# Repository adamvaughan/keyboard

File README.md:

Low profile, alice-like keyboard.

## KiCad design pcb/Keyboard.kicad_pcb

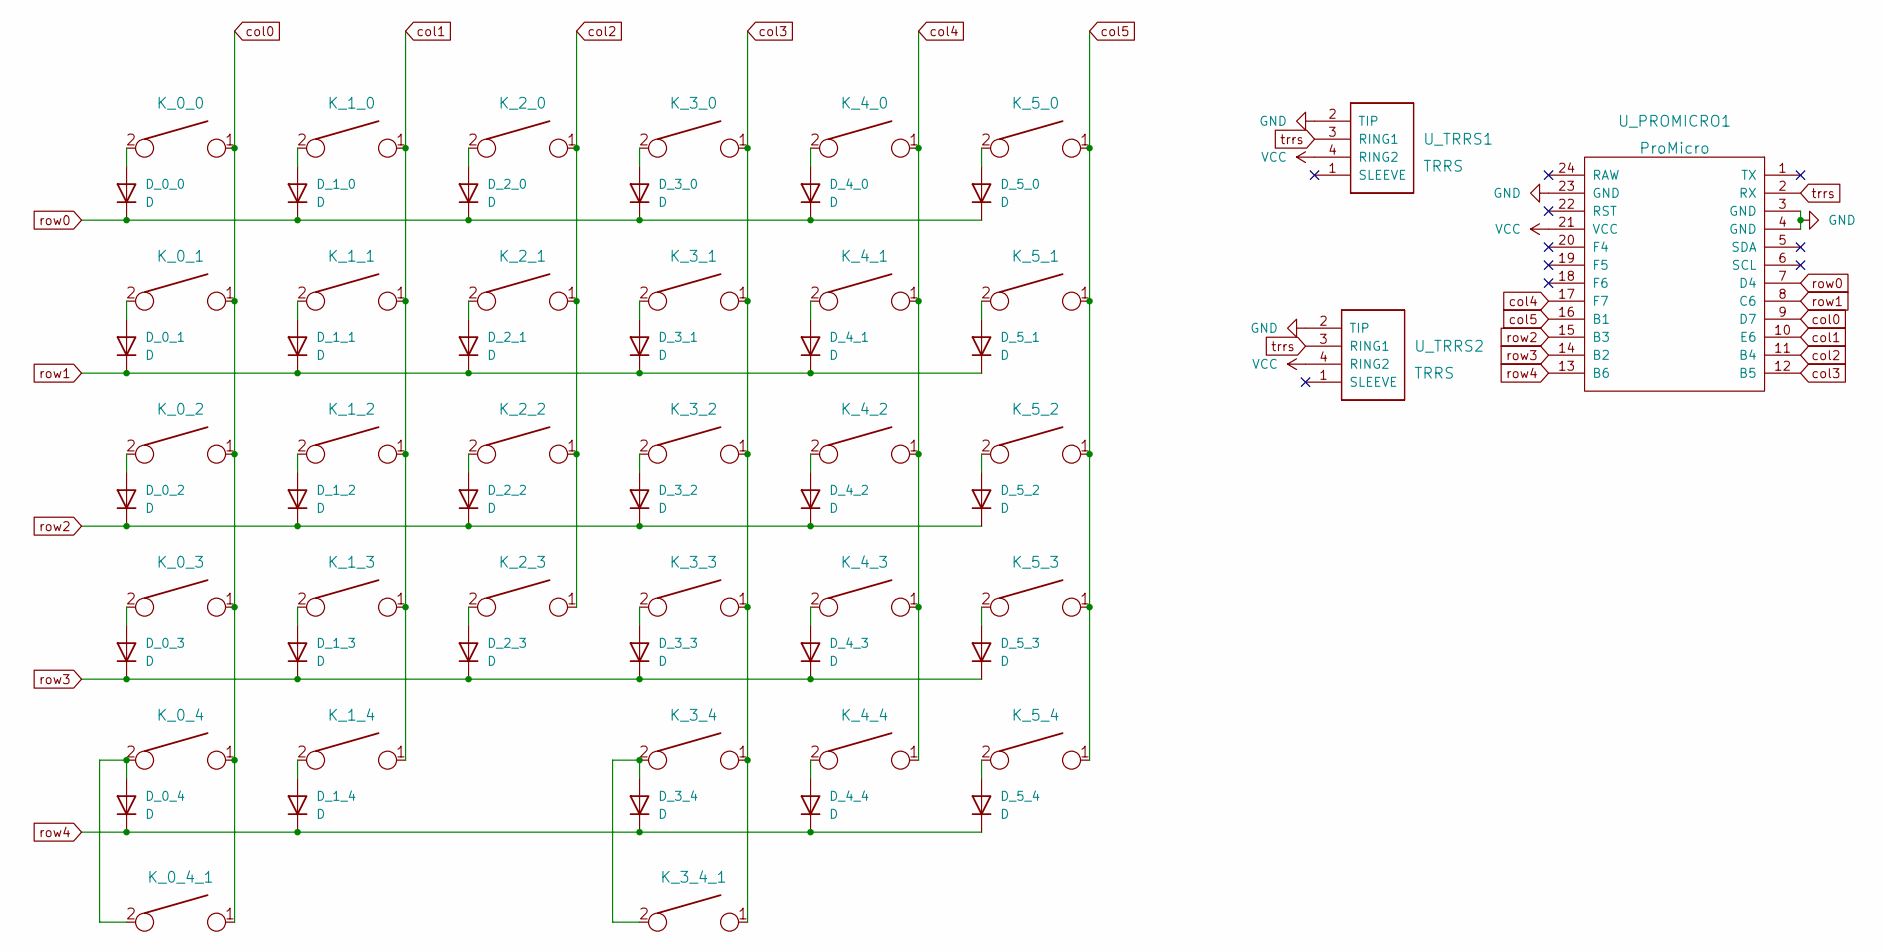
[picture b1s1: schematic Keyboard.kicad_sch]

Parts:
D_0_0, D_0_1, D_0_2, D_0_3, D_0_4, D_1_0, D_1_1, D_1_2, D_1_3, D_1_4, D_2_0, D_2_1, D_2_2, D_2_3, D_3_0, D_3_1, D_3_2, D_3_3, D_3_4, D_4_0, D_4_1, D_4_2, D_4_3, D_4_4, D_5_0, D_5_1, D_5_2, D_5_3, D_5_4: D; D_SOD123
K_0_0, K_0_1, K_0_2, K_0_3, K_0_4, K_0_4_1, K_1_0, K_1_1, K_1_2, K_1_3, K_1_4, K_2_0, K_2_1, K_2_2, K_2_3, K_3_0, K_3_1, K_3_2, K_3_3, K_3_4, K_3_4_1, K_4_0, K_4_1, K_4_2, K_4_3, K_4_4, K_5_0, K_5_1, K_5_2, K_5_3, K_5_4: KEYSW; SW_Hotswap_Kailh_Choc_V1_1.00u
U_PROMICRO1: ProMicro
U_TRRS1, U_TRRS2: TRRS; TRRS-PJ-320A

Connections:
GND: U_PROMICRO1.3 (GND), U_PROMICRO1.4 (GND), U_PROMICRO1.23 (GND), U_TRRS1.2 (TIP), U_TRRS2.2 (TIP)
unnamed: D_0_0.2 (A), K_0_0.2
unnamed: D_0_1.2 (A), K_0_1.2
unnamed: D_0_2.2 (A), K_0_2.2
unnamed: D_0_3.2 (A), K_0_3.2
unnamed: D_0_4.2 (A), K_0_4.2, K_0_4_1.2
unnamed: D_1_0.2 (A), K_1_0.2
unnamed: D_1_1.2 (A), K_1_1.2
unnamed: D_1_2.2 (A), K_1_2.2
unnamed: D_1_3.2 (A), K_1_3.2
unnamed: D_1_4.2 (A), K_1_4.2
unnamed: D_2_0.2 (A), K_2_0.2
unnamed: D_2_1.2 (A), K_2_1.2
unnamed: D_2_2.2 (A), K_2_2.2
unnamed: D_2_3.2 (A), K_2_3.2
unnamed: D_3_0.2 (A), K_3_0.2
unnamed: D_3_1.2 (A), K_3_1.2
unnamed: D_3_2.2 (A), K_3_2.2
unnamed: D_3_3.2 (A), K_3_3.2
unnamed: D_3_4.2 (A), K_3_4.2, K_3_4_1.2
unnamed: D_4_0.2 (A), K_4_0.2
unnamed: D_4_1.2 (A), K_4_1.2
unnamed: D_4_2.2 (A), K_4_2.2
unnamed: D_4_3.2 (A), K_4_3.2
unnamed: D_4_4.2 (A), K_4_4.2
unnamed: D_5_0.2 (A), K_5_0.2
unnamed: D_5_1.2 (A), K_5_1.2
unnamed: D_5_2.2 (A), K_5_2.2
unnamed: D_5_3.2 (A), K_5_3.2
unnamed: D_5_4.2 (A), K_5_4.2
VCC: U_PROMICRO1.21 (VCC), U_TRRS1.4 (RING2), U_TRRS2.4 (RING2)
col0: K_0_0.1, K_0_1.1, K_0_2.1, K_0_3.1, K_0_4.1, K_0_4_1.1, U_PROMICRO1.9 (D7)
col1: K_1_0.1, K_1_1.1, K_1_2.1, K_1_3.1, K_1_4.1, U_PROMICRO1.10 (E6)
col2: K_2_0.1, K_2_1.1, K_2_2.1, K_2_3.1, U_PROMICRO1.11 (B4)
col3: K_3_0.1, K_3_1.1, K_3_2.1, K_3_3.1, K_3_4.1, K_3_4_1.1, U_PROMICRO1.12 (B5)
col4: K_4_0.1, K_4_1.1, K_4_2.1, K_4_3.1, K_4_4.1, U_PROMICRO1.17 (F7)
col5: K_5_0.1, K_5_1.1, K_5_2.1, K_5_3.1, K_5_4.1, U_PROMICRO1.16 (B1)
row0: D_0_0.1 (K), D_1_0.1 (K), D_2_0.1 (K), D_3_0.1 (K), D_4_0.1 (K), D_5_0.1 (K), U_PROMICRO1.7 (D4)
row1: D_0_1.1 (K), D_1_1.1 (K), D_2_1.1 (K), D_3_1.1 (K), D_4_1.1 (K), D_5_1.1 (K), U_PROMICRO1.8 (C6)
row2: D_0_2.1 (K), D_1_2.1 (K), D_2_2.1 (K), D_3_2.1 (K), D_4_2.1 (K), D_5_2.1 (K), U_PROMICRO1.15 (B3)
row3: D_0_3.1 (K), D_1_3.1 (K), D_2_3.1 (K), D_3_3.1 (K), D_4_3.1 (K), D_5_3.1 (K), U_PROMICRO1.14 (B2)
row4: D_0_4.1 (K), D_1_4.1 (K), D_3_4.1 (K), D_4_4.1 (K), D_5_4.1 (K), U_PROMICRO1.13 (B6)
trrs: U_PROMICRO1.2 (RX), U_TRRS1.3 (RING1), U_TRRS2.3 (RING1)

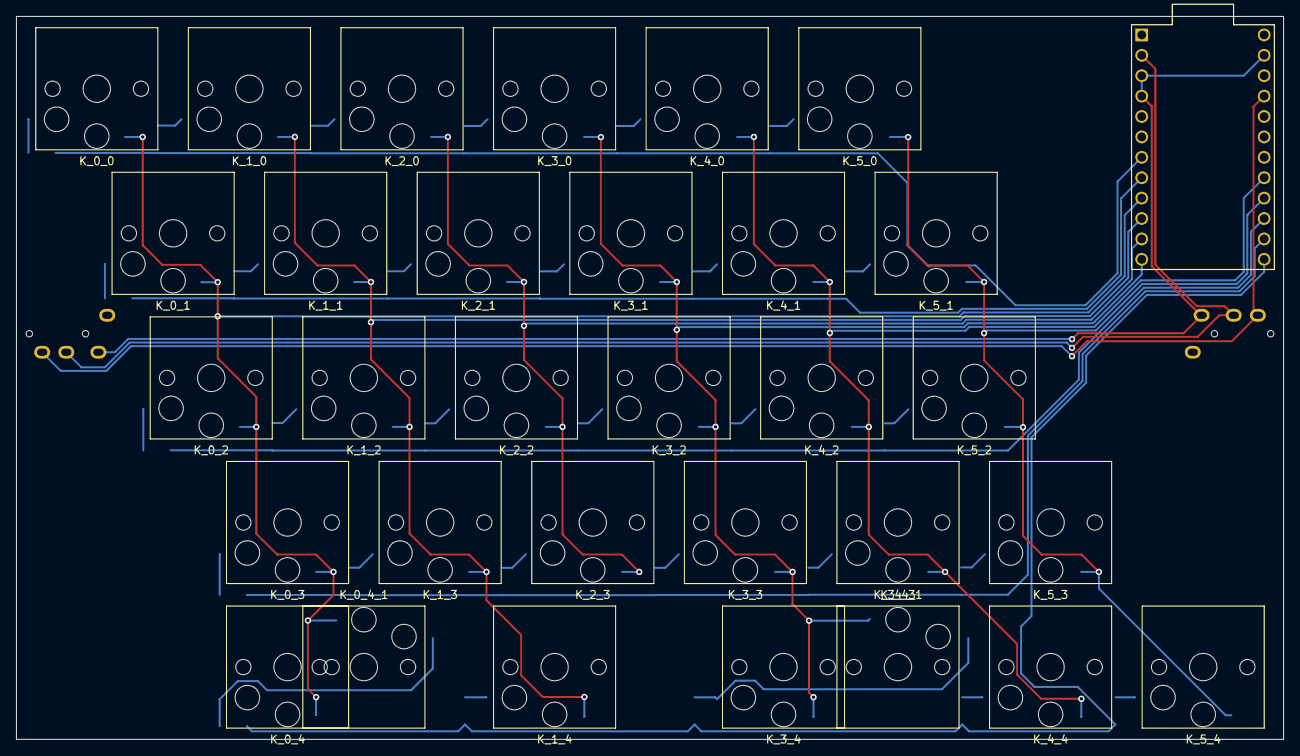
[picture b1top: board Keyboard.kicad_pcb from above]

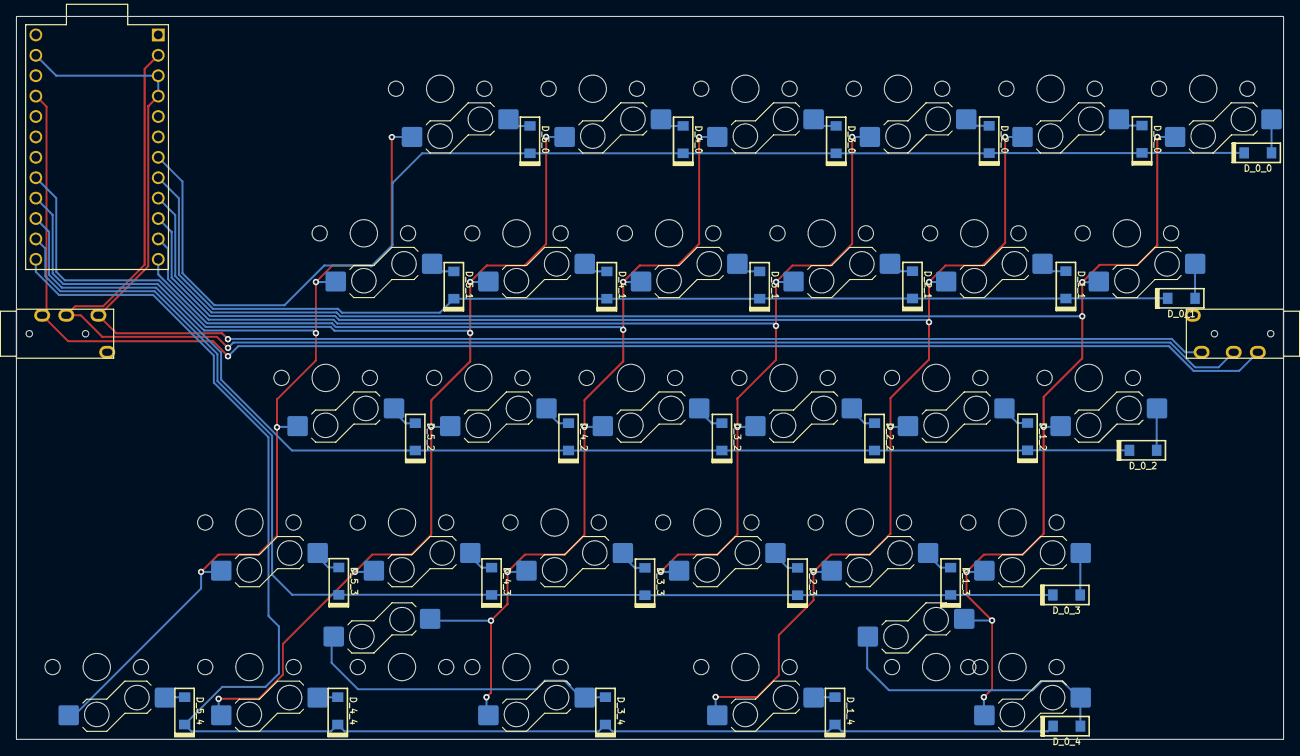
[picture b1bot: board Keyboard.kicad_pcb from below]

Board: 2 copper layers, 157.8 x 90.0 mm, 63 parts (31 on the bottom side), 43 nets.

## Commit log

2022-03-05 Initial commit.
2022-03-05 Add note about wrong serial pin.
    Wired this wrong. Needs to go to D0, D1, D2, D3, or E6.
2022-03-05 Add QMK configuration.
2022-03-05 Add readme.
2022-03-05 Fix TRRS jack wiring.
2022-03-06 Add dependency.
2022-10-09 Low profile alice-like.
2022-10-09 Remove old files.
